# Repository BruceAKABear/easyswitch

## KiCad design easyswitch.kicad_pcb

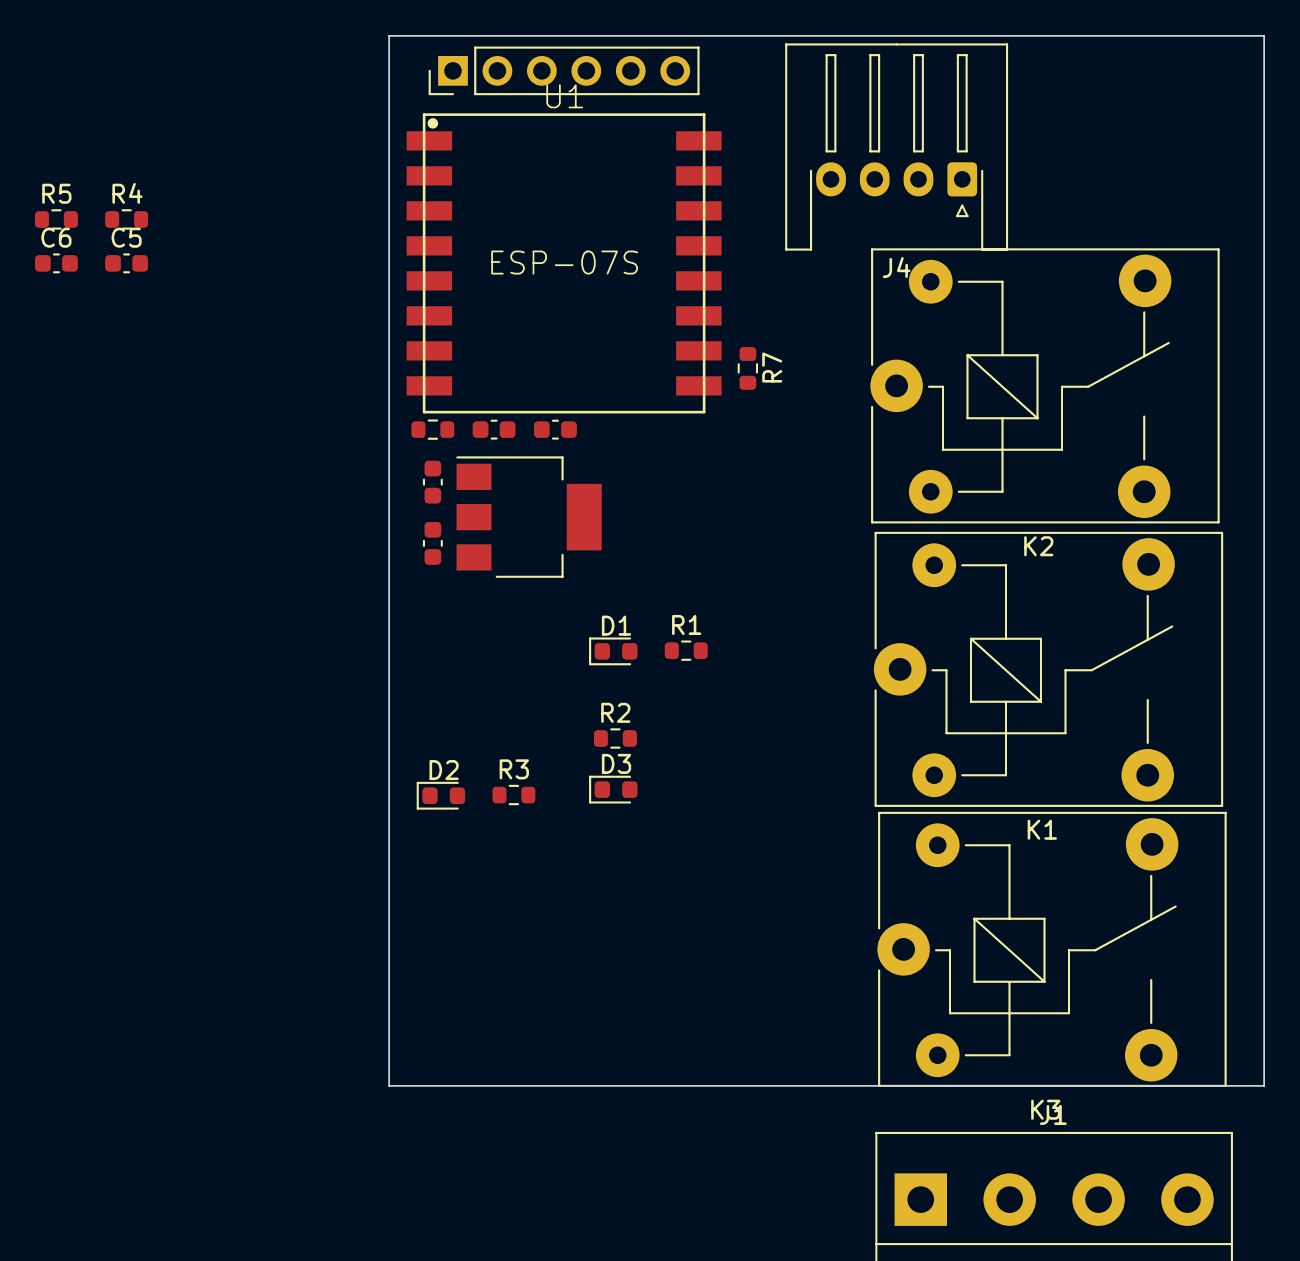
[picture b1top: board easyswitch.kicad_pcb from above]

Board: 2 copper layers, 50.0 x 60.0 mm, 24 parts (0 on the bottom side), 19 nets, no tracks yet.

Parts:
C1, C3, C4: 10uf; C_0603_1608Metric
C2, C5, C6: 0.1uf; C_0603_1608Metric
D1, D2, D3: D; D_0603_1608Metric
J1: Conn_01x04_Female; TerminalBlock_bornier-4_P5.08mm
J3: Conn_01x06_Female; PinHeader_1x06_P2.54mm_Vertical
J4: Conn_01x04_Female; JST_XH_S4B-XH-A-1_1x04_P2.50mm_Horizontal
K1, K2, K3: SANYOU_SRD_Form_C; Relay_SPDT_SANYOU_SRD_Series_Form_C
R1, R2, R3: 1k; R_0603_1608Metric
R4, R5, R6, R7: 10k; R_0603_1608Metric
U1: ESP-07S
U2: AMS1117-3.3; SOT-223-3_TabPin2

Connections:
220L: K1.1, K2.1, K3.1
+3V3: C1.2, C2.2, C4.1, R4.1, R5.1, R6.1, U1.8 (VCC), U2.2 (VO)
+5V: C3.1, J3.1, J4.1, U2.3 (VI)
BOOT: C6.1, J3.5, R5.2, U1.12 (GPIO0)
GND: C1.1, C2.1, C3.2, C4.2, C5.2, C6.2, J3.2, J4.2, R7.2, U1.9 (GND), U2.1 (GND)
LOAD_1: J1.2, K1.3
LOAD_2: J1.3, K2.3
LOAD_3: J1.4, K3.3
unnamed: D1.1 (K), K1.5
unnamed: D1.2 (A), K1.2
unnamed: D2.1 (K), K2.5
unnamed: D2.2 (A), K2.2
unnamed: D3.1 (K), K3.5
unnamed: D3.2 (A), K3.2
unnamed: R6.2, U1.3 (CH_PD)
unnamed: R7.1, U1.10 (GPIO15)
REST: C5.1, J3.6, R4.2, U1.1 (REST)
RX: J3.4, U1.15 (RXD)
TX: J3.3, U1.16 (TXD)

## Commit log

2022-05-07 init
